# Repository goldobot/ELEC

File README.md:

#ELEC
fichier source des cartes électronique

n'oubliez pas d'ajouter les éléments suivant à la liste gitignore si vous utiliser Altium:
#ignore altium log file
history
*/__Previews
__Previews
Project Logs*

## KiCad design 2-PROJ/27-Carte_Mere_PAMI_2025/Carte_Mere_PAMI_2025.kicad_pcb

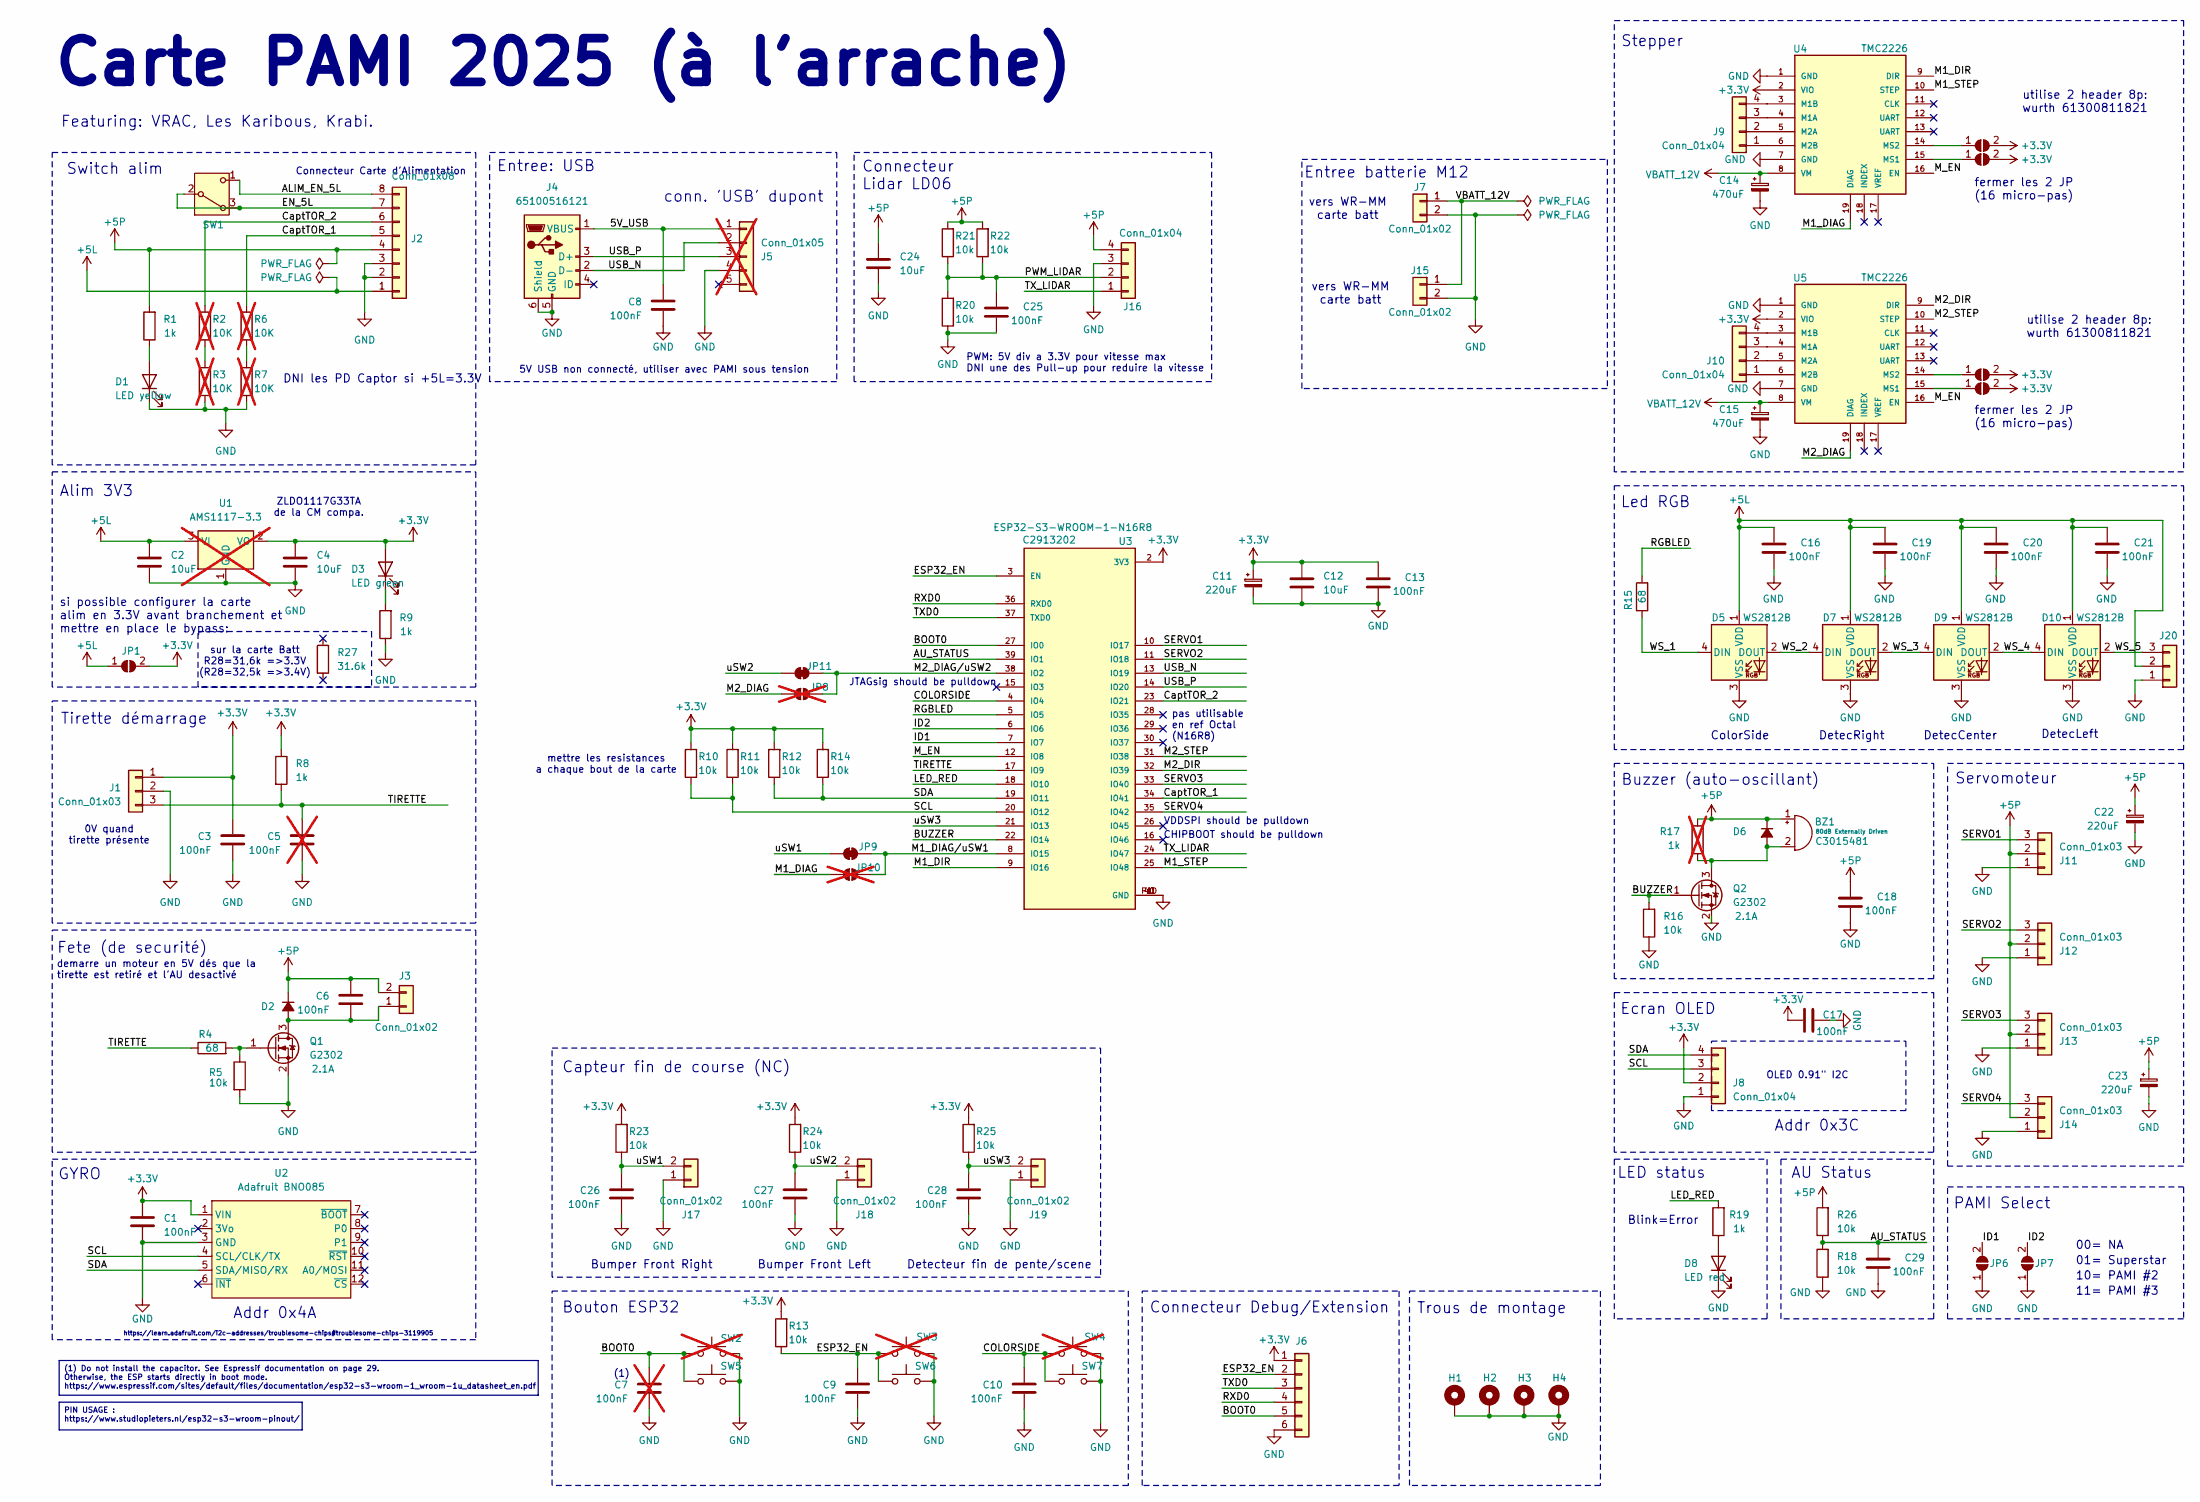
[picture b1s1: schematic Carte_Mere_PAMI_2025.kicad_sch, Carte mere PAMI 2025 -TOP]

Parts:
BZ1: Buzzer; Buzzer_TDK_PS1240P02BT_D12.2mm_H6.5mm; LCSC C3015481
C1, C3, C6, C8, C9, C10, C13, C16, C17, C18, C19, C20, C21, C25, C26, C27, C28, C29: 100nF; C_0603_1608Metric_Pad1.08x0.95mm_HandSolder; LCSC C14663
C2, C4, C12, C24: 10uF; C_0805_2012Metric; LCSC C440198
C5, C7: 100nF; C_0603_1608Metric_Pad1.08x0.95mm_HandSolder; LCSC C14663; not fitted
C11, C22, C23: 220uF; C_Radial_D6.3mm_H11.0mm_P2.50mm
C14, C15: 470uF; C_Radial_D8.0mm_H11.5mm_P3.50mm
D1: LED yellow; LED_0603_1608Metric; LCSC C2290
D2, D6: 1N4148W; D_SOD-123F; LCSC C81598
D3: LED green; LED_0603_1608Metric; LCSC C2290
D5, D7, D9, D10: WS2812B; LED_WS2812B_PLCC4_5.0x5.0mm_P3.2mm
D8: LED red; LED_0603_1608Metric; LCSC C2286
H1, H2, H3, H4: MountingHole_Pad; MountingHole_3.2mm_M3_Pad
J1, J11, J12, J13, J14, J20: Conn_01x03; PinHeader_1x03_P2.54mm_Vertical
J2: Conn_01x08; PinHeader_1x08_P2.54mm_Horizontal
J3, J17, J18, J19: Conn_01x02; PinHeader_1x02_P2.54mm_Vertical
J4: 65100516121; USB_Mini-B_Wuerth_65100516121_Horizontal; LCSC C720611
J5: Conn_01x05; PinHeader_1x05_P2.54mm_Vertical; not fitted
J6: Conn_01x06; PinHeader_1x06_P2.54mm_Vertical
J7, J15: Conn_01x02; SolderWire-0.75sqmm_1x02_P4.8mm_D1.25mm_OD2.3mm
J8: Conn_01x04; Ecran_OLED0.9_Waveshare
J9, J10: Conn_01x04; PinHeader_1x04_P2.54mm_Horizontal
J16: Conn_01x04; PinHeader_1x04_P2.54mm_Vertical
JP1, JP6: ID1; SolderJumper-2_P1.3mm_Open_RoundedPad1.0x1.5mm
JP2, JP4: MS2; SolderJumper-2_P1.3mm_Open_RoundedPad1.0x1.5mm
JP3, JP5: MS1; SolderJumper-2_P1.3mm_Open_RoundedPad1.0x1.5mm
JP7: ID2; SolderJumper-2_P1.3mm_Open_RoundedPad1.0x1.5mm
JP8, JP10: SolderJumper_2_Bridged; R_0402_1005Metric; not fitted
JP9, JP11: SolderJumper_2_Bridged; R_0402_1005Metric_jumperClosed
Q1, Q2: G2302; SOT-23; LCSC C20917
R1, R9, R19: 1k; R_0603_1608Metric_Pad0.98x0.95mm_HandSolder
R2, R3, R6, R7: 10K; R_0603_1608Metric_Pad0.98x0.95mm_HandSolder; LCSC C25804; not fitted
R4, R15: 68; R_0603_1608Metric_Pad0.98x0.95mm_HandSolder; LCSC C23182
R5, R10, R11, R12, R13, R14, R16, R18, R20, R21, R22, R23, R24, R25, R26: 10k; R_0603_1608Metric_Pad0.98x0.95mm_HandSolder; LCSC C25804
R8: 1k; R_0603_1608Metric_Pad0.98x0.95mm_HandSolder; LCSC C21190
R17: 1k; R_0603_1608Metric_Pad0.98x0.95mm_HandSolder; not fitted
R27: 31.6k; R_0603_1608Metric_Pad0.98x0.95mm_HandSolder; Mouser 603-AC0603FR-0731K6L
SW1: SW_DPST_x2; SW_Slide_SPDT_Straight_CK_OS102011MS2Q
SW2, SW3, SW4: SW_Push; SW_Push_1P1T_XKB_TS-1187A; LCSC C318884; not fitted
SW5, SW6, SW7: SW_Push; SW_Push_1TS009xxxx-xxxx-xxxx_6x6x5mm; Mouser 710-430133050816
U1: AMS1117-3.3; SOT-223-3_TabPin2; LCSC C7376; not fitted
U2: Adafruit BNO085
U3: ESP32-S3-WROOM-1-N16R8; PARTREV v1.0; LCSC C2913202
U4, U5: TMC2226; TMC2226_SHIELD

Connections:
+3.3V: C1.1, C3.1, C4.1, C11.1, C12.1, C13.1, C17.1, D3.2 (A), J1.1, J6.1, J8.2, JP1.2 (B), JP2.2 (B), JP3.2 (B), JP4.2 (B), JP5.2 (B), R8.1, R10.2, R11.2, R12.2, R13.2, R14.2, R23.2, R24.2, R25.2, U1.2 (VO), U2.1 (VIN), U3.2 (3V3), U4.2 (VIO), U5.2 (VIO)
+5L: C2.1, C16.1, C19.1, C20.1, C21.1, D5.1 (VDD), D7.1 (VDD), D9.1 (VDD), D10.1 (VDD), J2.1, J20.2, JP1.1 (A), U1.3 (VI)
+5P: BZ1.1 (+), C6.1, C18.1, C22.1, C23.1, C24.1, D2.1 (K), D6.1 (K), J2.4, J3.2, J11.2, J12.2, J13.2, J14.2, J16.4, R1.2, R17.2, R21.2, R22.2, R26.2
/5V_USB: C8.1, J4.1 (VBUS), J5.1
/ALIM_EN_5L: J2.8, SW1.1 (C)
/AU_STATUS: C29.1, R18.2, R26.1, U3.39 (IO1)
/BOOT0: C7.1, J6.5, SW2.1, SW5.1, U3.27 (IO0)
/BUZZER: Q2.1 (G), R16.2, U3.22 (IO14)
/COLORSIDE: C10.1, SW4.1, SW7.1, U3.4 (IO4)
/CaptTOR_1: J2.5, R6.2, U3.34 (IO41)
/CaptTOR_2: J2.6, R2.2, U3.23 (IO21)
/EN_5L: J2.7, SW1.2 (B), SW1.3 (A)
/ESP32_EN: C9.1, J6.2, R13.1, SW3.1, SW6.1, U3.3 (EN)
/ID1: JP6.2 (B), U3.7 (IO7)
/ID2: JP7.2 (B), U3.6 (IO6)
/LED_RED: R19.2, U3.18 (IO10)
/M1_DIAG: JP10.1 (A), U4.19 (DIAG)
/M1_DIAG/uSW1: JP9.2 (B), JP10.2 (B), U3.8 (IO15)
/M1_DIR: U3.9 (IO16), U4.9 (DIR)
/M1_STEP: U3.25 (IO48), U4.10 (STEP)
/M2_DIAG: JP8.1 (A), U5.19 (DIAG)
/M2_DIAG/uSW2: JP8.2 (B), JP11.2 (B), U3.38 (IO2)
/M2_DIR: U3.32 (IO39), U5.9 (DIR)
/M2_STEP: U3.31 (IO38), U5.10 (STEP)
/M_EN: U3.12 (IO8), U4.16 (EN), U5.16 (EN)
/PWM_LIDAR: C25.1, J16.2, R20.2, R21.1, R22.1
/RGBLED: R15.2, U3.5 (IO5)
/RXD0: J6.4, U3.36 (RXD0)
/SCL: J8.3, R10.1, R11.1, U2.4 (SCL/CLK/TX), U3.20 (IO12)
/SDA: J8.4, R12.1, R14.1, U2.5 (SDA/MISO/RX), U3.19 (IO11)
/SERVO1: J11.3, U3.10 (IO17)
/SERVO2: J12.3, U3.11 (IO18)
/SERVO3: J13.3, U3.33 (IO40)
/SERVO4: J14.3, U3.35 (IO42)
/TIRETTE: C5.1, J1.3, R4.1, R8.2, U3.17 (IO9)
/TXD0: J6.3, U3.37 (TXD0)
/TX_LIDAR: J16.1, U3.24 (IO47)
/USB_N: J4.2 (D-), J5.2, U3.13 (IO19)
/USB_P: J4.3 (D+), J5.3, U3.14 (IO20)
/WS_1: D5.4 (DIN), R15.1
/WS_2: D5.2 (DOUT), D7.4 (DIN)
/WS_3: D7.2 (DOUT), D9.4 (DIN)
/WS_4: D9.2 (DOUT), D10.4 (DIN)
/WS_5: D10.2 (DOUT), J20.3
/uSW1: C26.1, J17.2, JP9.1 (A), R23.1
/uSW2: C27.1, J18.2, JP11.1 (A), R24.1
/uSW3: C28.1, J19.2, R25.1, U3.21 (IO13)
GND: C1.2, C2.2, C3.2, C4.2, C5.2, C7.2, C8.2, C9.2, C10.2, C11.2, C12.2, C13.2, C14.2, C15.2, C16.2, C17.2, C18.2, C19.2, C20.2, C21.2, C22.2, C23.2, C24.2, C25.2, C26.2, C27.2, C28.2, C29.2, D1.1 (K), D5.3 (VSS), D7.3 (VSS), D8.1 (K), D9.3 (VSS), D10.3 (VSS), H1.1, H2.1, H3.1, H4.1, J1.2, J2.2, J2.3, J4.5 (GND), J4.6 (Shield), J5.4, J6.6, J7.2, J8.1, J11.1, J12.1, J13.1, J14.1, J15.2, J16.3, J17.1, J18.1, J19.1, J20.1, JP6.1 (A), JP7.1 (A), Q1.2 (S), Q2.2 (S), R3.1, R5.2, R7.1, R9.1, R16.1, R18.1, R20.1, SW2.2, SW3.2, SW4.2, SW5.2, SW6.2, SW7.2, U1.1 (GND), U2.3 (GND), U3.1 (GND), U3.40 (GND), U3.PAD (GND), U4.1 (GND), U4.7 (GND), U5.1 (GND), U5.7 (GND)
unnamed: BZ1.2 (-), D6.2 (A), Q2.3 (D), R17.1
unnamed: D1.2 (A), R1.1
unnamed: C6.2, D2.2 (A), J3.1, Q1.3 (D)
unnamed: D3.1 (K), R9.2
unnamed: D8.2 (A), R19.1
unnamed: J9.1, U4.6 (M2B)
unnamed: J9.2, U4.5 (M2A)
unnamed: J9.3, U4.4 (M1A)
unnamed: J9.4, U4.3 (M1B)
unnamed: J10.1, U5.6 (M2B)
unnamed: J10.2, U5.5 (M2A)
unnamed: J10.3, U5.4 (M1A)
unnamed: J10.4, U5.3 (M1B)
unnamed: JP2.1 (A), U4.14 (MS2)
unnamed: JP3.1 (A), U4.15 (MS1)
unnamed: JP4.1 (A), U5.14 (MS2)
unnamed: JP5.1 (A), U5.15 (MS1)
unnamed: Q1.1 (G), R4.2, R5.1
unnamed: R2.1, R3.2
unnamed: R6.1, R7.2
VBATT_12V: C14.1, C15.1, J7.1, J15.1, U4.8 (VM), U5.8 (VM)

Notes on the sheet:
(1) Do not install the capacitor. See Espressif documentation on page 29. Otherwise, the ESP starts directly in boot mode. https://www.espressif.com/sites/default/files/documentation/esp32-s3-wroom-1_wroom-1u_datasheet_en.pdf
PIN USAGE : https://www.studiopieters.nl/esp32-s3-wroom-pinout/
Stepper
Connecteur Carte d'Alimentation
Tirette démarrage
DetecLeft
Servomoteur
GYRO
fermer les 2 JP (16 micro-pas)
vers WR-MM carte batt
CHIPBOOT should be pulldown
Trous de montage
LED status
ZLDO1117G33TA de la CM compa.
demarre un moteur en 5V dés que la tirette est retiré et l'AU desactivé
Featuring: VRAC, Les Karibous, Krabi.
Blink=Error
Addr 0x4A
Carte PAMI 2025 (à l'arrache)
OLED 0.91" I2C
Ecran OLED
00= NA
0V quand tirette présente
Alim 3V3
AU Status
utilise 2 header 8p: wurth 61300811821
Fete (de securité)
Led RGB
pas utilisable en ref Octal (N16R8)
Capteur fin de course (NC)
Bumper Front Right
DetecCenter
ColorSide
Connecteur Debug/Extension
Addr 0x3C
conn. 'USB' dupont
mettre les resistances a chaque bout de la carte
11= PAMI #3
Connecteur Lidar LD06
Entree batterie M12

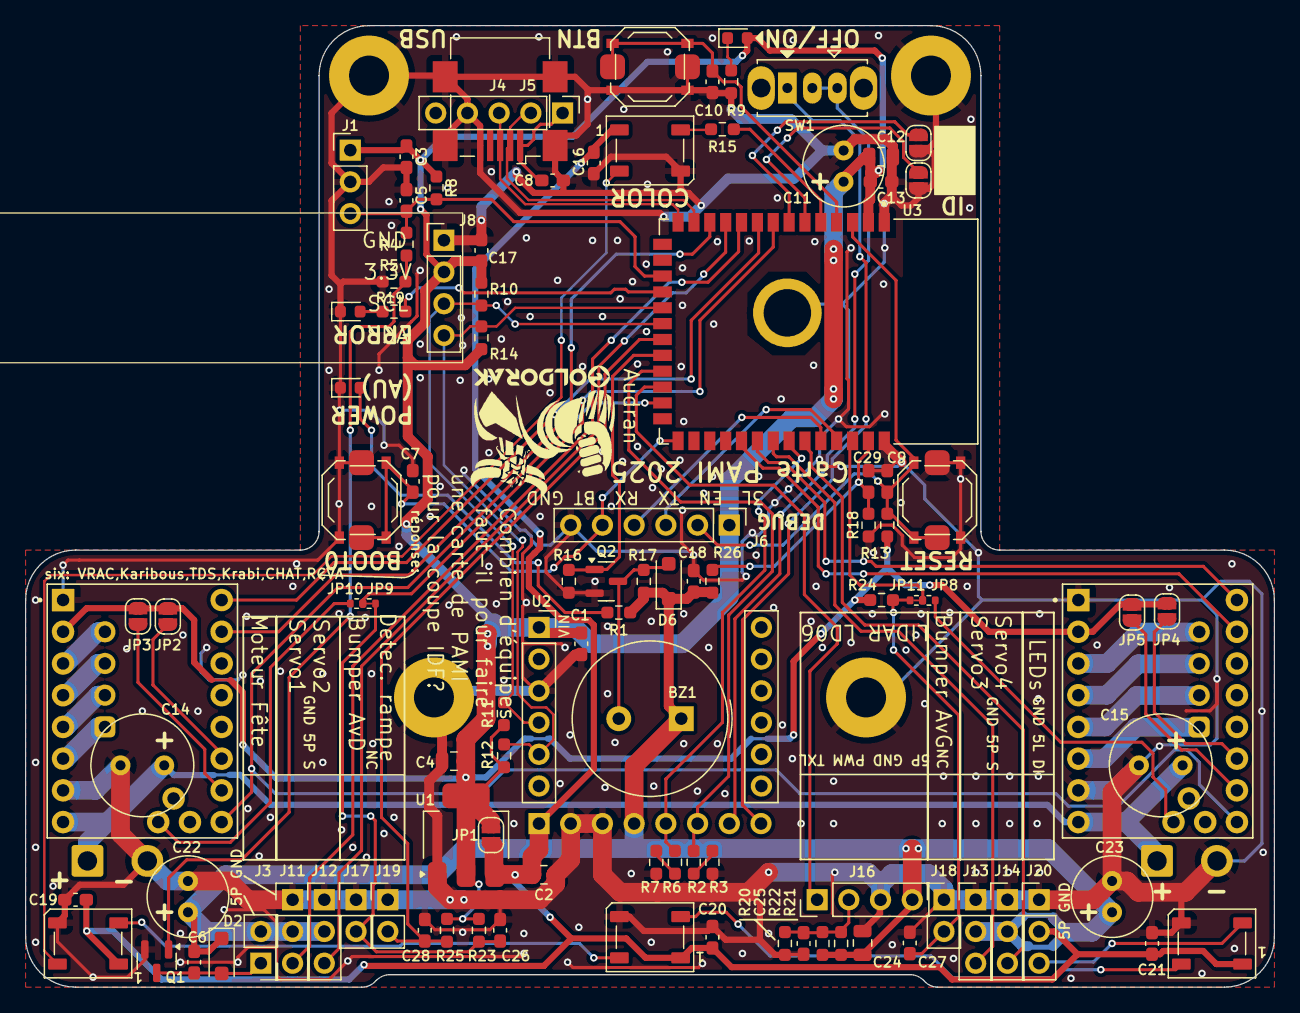
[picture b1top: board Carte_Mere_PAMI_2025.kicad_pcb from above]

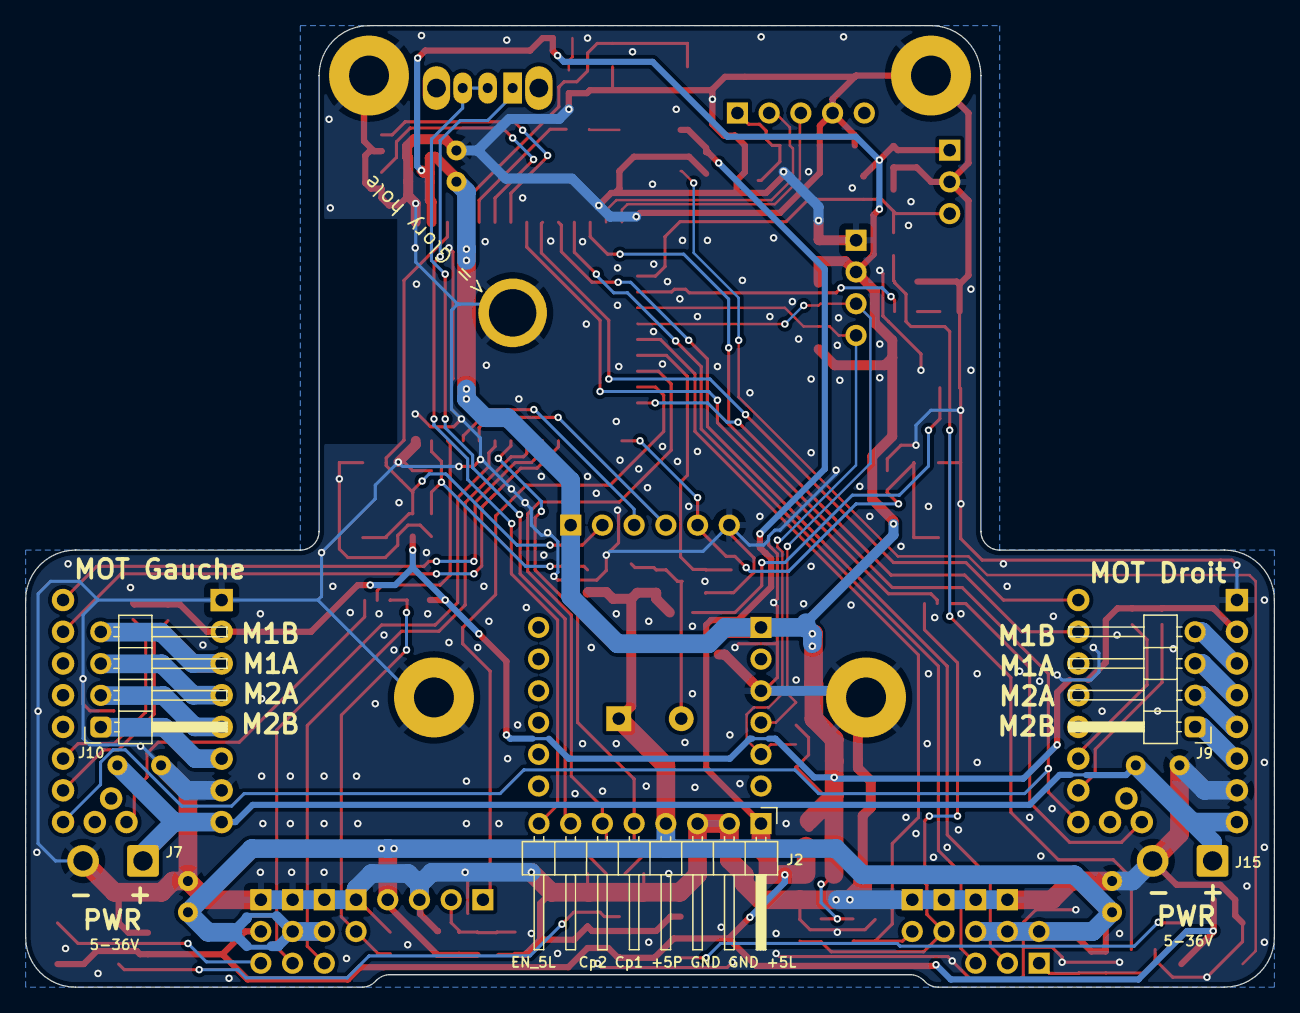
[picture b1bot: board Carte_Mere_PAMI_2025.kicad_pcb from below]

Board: 2 copper layers, 100.0 x 77.0 mm, 114 parts (5 on the bottom side), 69 nets.

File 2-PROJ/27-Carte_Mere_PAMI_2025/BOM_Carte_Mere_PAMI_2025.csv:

"Reference";"Value";"Qty";"DNP";"Mouser"
"BZ1";"Buzzer";"1";"";""
"C1,C3,C6,C8,C9,C10,C13,C16,C17,C18,C19,C20,C21,C25,C26,C27,C28,C29";"100nF";"18";"";""
"C2,C4,C12,C24";"10uF";"4";"";"81-GRM21BR61H106KE3L"
"C11,C22,C23";"220uF";"3";"";""
"C14,C15";"470uF";"2";"";""
"D1";"LED yellow";"1";"";"710-150060YS75000"
"D2,D6";"1N4148W";"2";"";"621-1N4148W-F"
"D3";"LED green";"1";"";"710-150060VS75000"
"D5,D7,D9,D10";"WS2812B";"4";"";""
"D8";"LED red";"1";"";""
"J1,J11,J12,J13,J14,J20";"Conn_01x03";"6";"";""
"J2";"Conn_01x08";"1";"";""
"J3,J17,J18,J19";"Conn_01x02";"4";"";""
"J4";"65100516121";"1";"";"710-65100516121"
"J6";"Conn_01x06";"1";"";""
"J8,J9,J10,J16";"Conn_01x04";"4";"";""
"JP1,JP6";"ID1";"2";"";""
"JP2,JP4";"MS2";"2";"";""
"JP3,JP5";"MS1";"2";"";""
"JP7";"ID2";"1";"";""
"Q1,Q2";"G2302";"2";"";"621-DMG2302UK-7"
"R1,R8,R9,R19";"1k";"4";"";""
"R4,R15";"68";"2";"";"603-RC0603FR-1068RL"
"R5,R10,R11,R12,R13,R14,R16,R18,R20,R21,R22,R23,R24,R25,R26";"10k";"15";"";""
"R27";"31.6k";"1";"";"603-AC0603FR-0731K6L"
"SW1";"SW_DPST_x2";"1";"";""
"SW5,SW6,SW7";"SW_Push";"3";"";"710-430133050816"
"U2";"Adafruit BNO085";"1";"";""
"U3";"ESP32-S3-WROOM-1-N16R8";"1";"";""
"U4,U5";"TMC2226";"2";"";""

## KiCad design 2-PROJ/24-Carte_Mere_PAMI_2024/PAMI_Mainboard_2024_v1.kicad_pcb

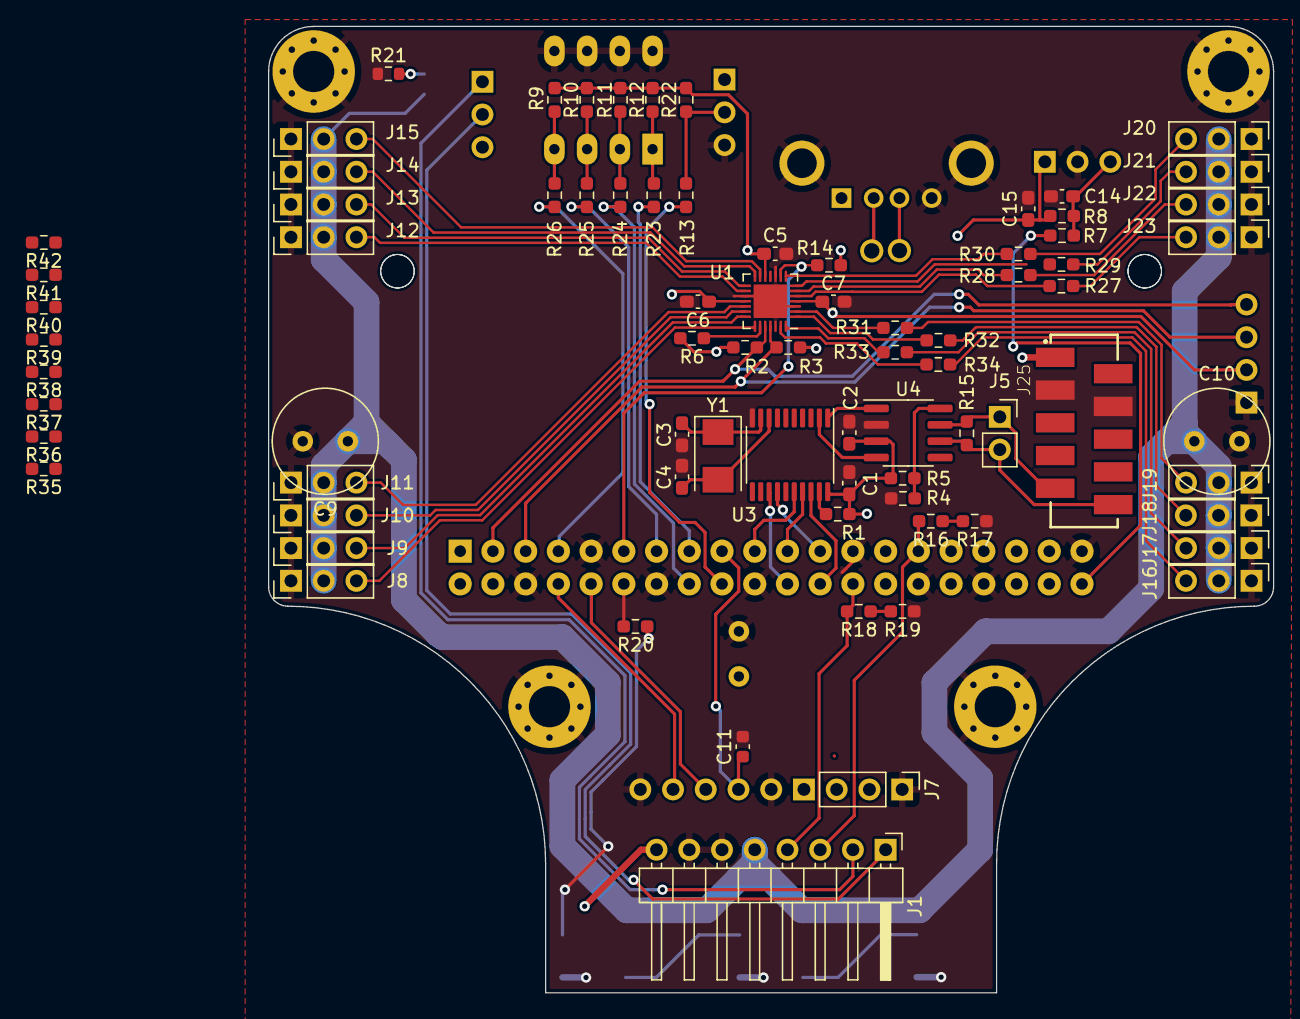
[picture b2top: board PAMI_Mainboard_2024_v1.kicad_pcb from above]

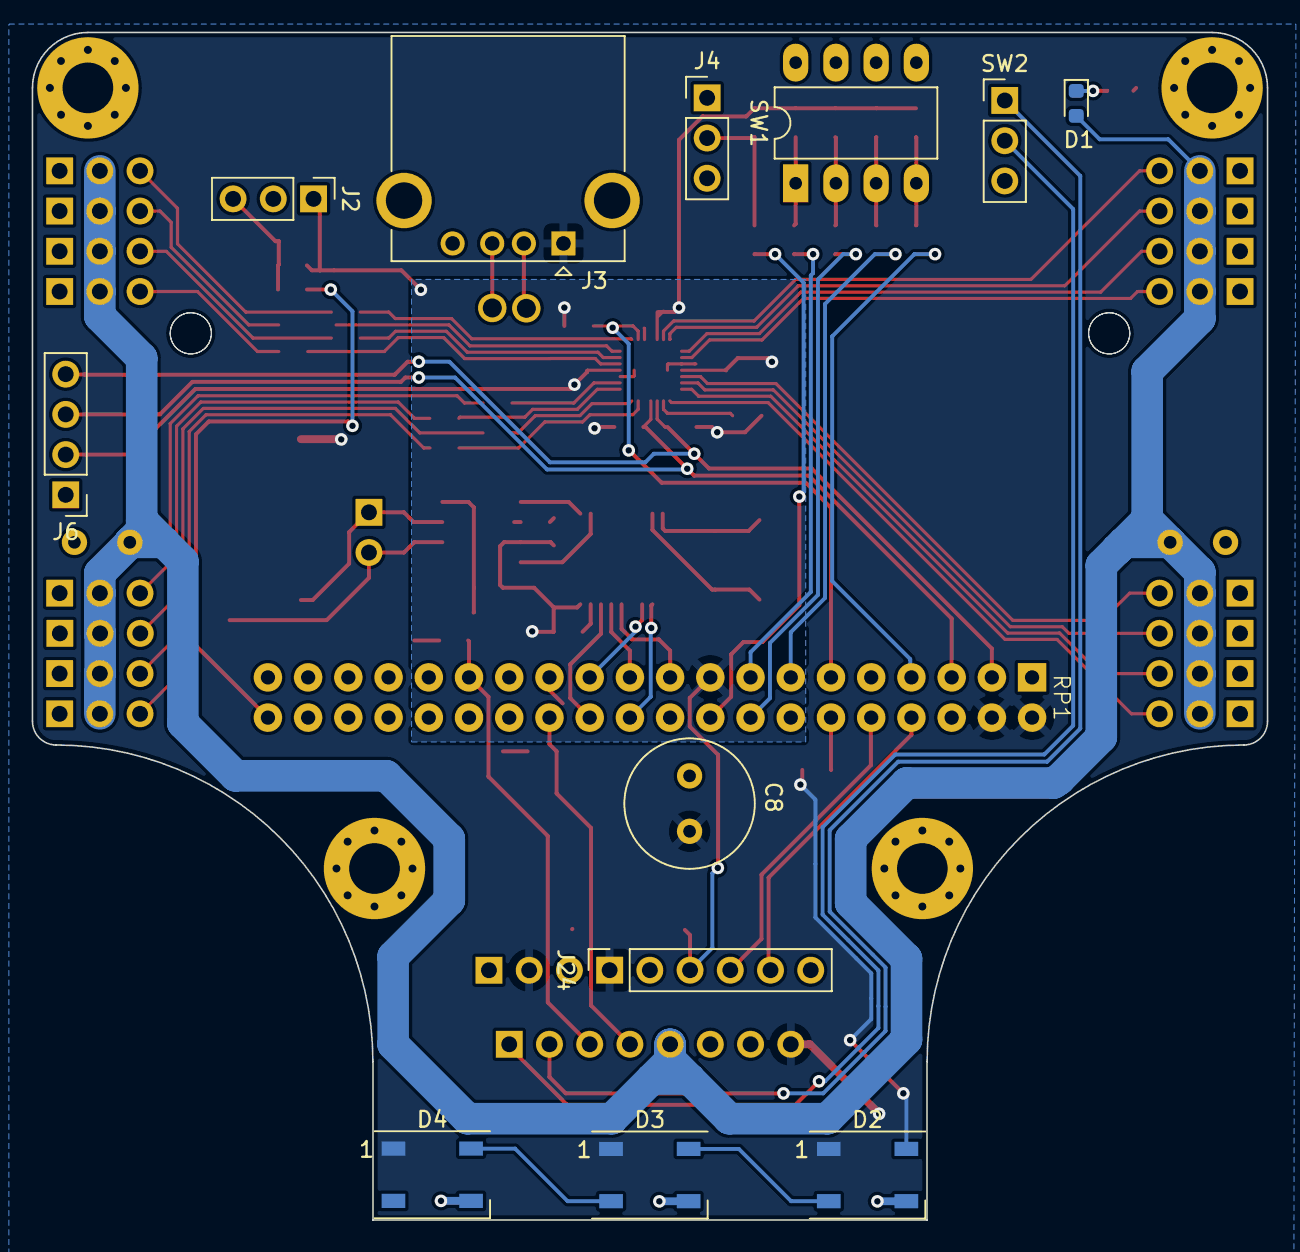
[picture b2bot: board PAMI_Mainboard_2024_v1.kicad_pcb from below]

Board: 2 copper layers, 78.0 x 75.0 mm, 96 parts (14 on the bottom side), 81 nets.

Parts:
C1, C2, C5, C6, C7, C14, C15: 100nF; C_0603_1608Metric_Pad1.08x0.95mm_HandSolder
C3, C4: 22pF; C_0603_1608Metric_Pad1.08x0.95mm_HandSolder
C8, C9, C10: 470uF; C_Radial_D8.0mm_H11.5mm_P3.50mm
C11: 100nF; C_0603_1608Metric
D1: LED; LED_0603_1608Metric
D2, D3, D4: WS2812B; LED_WS2812B_PLCC4_5.0x5.0mm_P3.2mm
H1, H2, H3, H4: MountingHole_Pad; MountingHole_3.2mm_M3_Pad_Via
J1: Conn_01x08; PinHeader_1x08_P2.54mm_Horizontal
J2, J4, J7, J8, J9, J10, J11, J12, J13, J14, J15, J16, J17, J18, J19, J20, J21, J22, J23: Conn_01x03; PinHeader_1x03_P2.54mm_Vertical
J3: USB_A; USB_A_CONNFLY_DS1095-WNR0
J5: Conn_01x02; PinSocket_1x02_P2.54mm_Vertical
J6: Conn_01x04; PinHeader_1x04_P2.54mm_Vertical
J24: Conn_01x06; PinSocket_1x06_P2.54mm_Vertical
J25: Conn_02x05_Odd_Even; 690357281076
R1, R2, R3, R4, R5, R6, R8, R9, R10, R11, R12, R14, R16, R17, R18, R19, R22: 10K; R_0603_1608Metric_Pad0.98x0.95mm_HandSolder
R7, R20: 68; R_0603_1608Metric_Pad0.98x0.95mm_HandSolder
R13, R23, R24, R25, R26, R27, R28, R29, R30, R31, R32, R33, R34, R35, R36, R37, R38, R39, R40, R41, R42: 1K; R_0603_1608Metric_Pad0.98x0.95mm_HandSolder
R15: 120; R_0603_1608Metric_Pad0.98x0.95mm_HandSolder
R21: 1K; R_0603_1608Metric
RP1: Raspberry_Pi_Zero
RP_USB1: Raspberry_Pi_Zero_USB_Pads
SW1: SW_DIP_x04; DIP-8_W7.62mm_LongPads
SW2: SW_DPST_x2; PinHeader_1x03_P2.54mm_Vertical
U1: QFN-28-1EP_4x4mm_P0.4mm_EP2.6x2.6mm_ThermalVias
U3: MCP2515-xST; TSSOP-20_4.4x6.5mm_P0.65mm
U4: MCP2551-I-SN; SOIC-8_3.9x4.9mm_P1.27mm
Y1: 16 MHz; Crystal_SMD_5032-2Pin_5.0x3.2mm

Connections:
+3.3VP: C1.1, C2.1, C5.1, C6.1, C7.1, C11.1, C15.1, J2.1, J6.2, J24.3, R1.2, R2.2, R3.2, R4.2, R6.2, R8.2, R9.2, R10.2, R11.2, R12.2, R14.2, R22.2, RP1.17 (3V3), U1.4 (VCC1), U1.12 (VDDM), U1.18 (VCC2), U3.20 (VDD), U4.3 (VDD)
+5P: C9.1, C10.1, D1.2 (A), J1.5, J8.2, J9.2, J10.2, J11.2, J12.2, J13.2, J14.2, J15.2, J16.2, J17.2, J18.2, J19.2, J20.2, J21.2, J22.2, J23.2
+5V: C8.1, D2.1 (VDD), D3.1 (VDD), D4.1 (VDD), J1.8, J3.1 (VBUS), J7.2, J24.1, J25.1, RP1.2 (5V), RP1.4 (5V)
/ALIM_EN_5L: J1.1, SW2.2 (B)
/CAN/CANH: J5.1, J25.9, R15.2, U4.7 (CANH)
/CAN/CANL: J5.2, J25.10, R15.1, U4.6 (CANL)
/CAN/CE: RP1.24 (GPIO8/SPI0_CE0), U3.18 (~CS)
/CAN/MISO: RP1.21 (GPIO9/SPI0_MISO), U3.17 (SO)
/CAN/MOSI: RP1.19 (GPIO10/SPI0_MOSI), U3.16 (SI)
/CAN/SCK: RP1.23 (GPIO11/SPI0_SCK), U3.14 (SCK)
/CaptTOR_1: J1.4, R18.2, RP1.26 (GPIO7/SPI0_CE1)
/CaptTOR_2: J1.3, R16.2, RP1.29 (GPIO5/GPCLK1)
/EN_5L: J1.2, SW2.1 (A)
/INT_CAN: RP1.22 (GPIO25), U3.13 (~INT)
/INT_SX: R14.1, RP1.11 (GPIO17/SPI1_CE1), U1.9 (INT)
/SIDE: R13.2, RP1.18 (GPIO24)
/SX1509/SCL: J6.3, R3.1, RP1.5 (GPIO3/I2C1_SCL), U1.25 (SCL)
/SX1509/SDA: J6.4, R2.1, RP1.3 (GPIO2/I2C1_SDA), U1.24 (SDA)
/SX1509/SX_IO_0: R34.1, U1.27 (IO_0)
/SX1509/SX_IO_1: R33.1, U1.28 (IO_1)
/SX1509/SX_IO_2: R32.1, U1.1 (IO_2)
/SX1509/SX_IO_3: R31.1, U1.2 (IO_3)
/SX1509/SX_IO_4: R27.1, U1.5 (IO_4)
/SX1509/SX_IO_5: R28.1, U1.6 (IO_5)
/SX1509/SX_IO_6: R29.1, U1.7 (IO_6)
/SX1509/SX_IO_7: R30.1, U1.8 (IO_7)
/SX1509/SX_IO_8: R42.2, U1.13 (IO_8)
/SX1509/SX_IO_9: R41.2, U1.14 (IO_9)
/SX1509/SX_IO_10: R40.2, U1.15 (IO_10)
/SX1509/SX_IO_11: R39.2, U1.16 (IO_11)
/SX1509/SX_IO_12: R38.2, U1.19 (IO_12)
/SX1509/SX_IO_13: R37.2, U1.20 (IO_13)
/SX1509/SX_IO_14: R36.2, U1.21 (IO_14)
/SX1509/SX_IO_15: R35.2, U1.22 (IO_15)
/TIRETTE: R7.2, RP1.40 (GPIO21/SPI1_SCK)
/WS2812B: R20.2, RP1.12 (GPIO18/SPI1_CE0)
GND: C1.2, C2.2, C3.2, C4.2, C5.2, C6.2, C7.2, C8.2, C9.2, C10.2, C11.2, C14.2, C15.2, D2.3 (VSS), D3.3 (VSS), D4.3 (VSS), H1.1, H2.1, H3.1, H4.1, J1.6, J1.7, J2.2, J3.4 (GND), J3.5 (Shield), J4.3, J6.1, J7.1, J8.1, J9.1, J10.1, J11.1, J12.1, J13.1, J14.1, J15.1, J16.1, J17.1, J18.1, J19.1, J20.1, J21.1, J22.1, J23.1, J24.2, J24.6, J25.3, J25.4, R5.1, R17.1, R19.1, R21.1, RP1.6 (GND), RP1.9 (GND), RP1.14 (GND), RP1.20 (GND), RP1.25 (GND), RP1.30 (GND), RP1.34 (GND), RP1.39 (GND), SW1.5, SW1.6, SW1.7, SW1.8, U1.3 (GND), U1.10 (ADDR1), U1.17 (GND), U1.26 (ADDR0), U1.29 (GND_PAD), U3.10 (VSS), U4.2 (VSS)
unnamed: D1.1 (K), R21.2
unnamed: D2.4 (DIN), R20.1
unnamed: D2.2 (DOUT), D3.4 (DIN)
unnamed: D3.2 (DOUT), D4.4 (DIN)
unnamed: D4.2 (DOUT), J7.3
unnamed: C14.1, J2.3, R7.1, R8.1
unnamed: J3.3 (D+), RP_USB1.1 (USB_DP)
unnamed: J3.2 (D-), RP_USB1.2 (USB_DM)
unnamed: J4.2, R13.1, R22.1
unnamed: J8.3, R35.1
unnamed: J9.3, R36.1
unnamed: J10.3, R37.1
unnamed: J11.3, R38.1
unnamed: J12.3, R39.1
unnamed: J13.3, R40.1
unnamed: J14.3, R41.1
unnamed: J15.3, R42.1
unnamed: J16.3, R34.2
unnamed: J17.3, R33.2
unnamed: J18.3, R32.2
unnamed: J19.3, R31.2
unnamed: J20.3, R27.2
unnamed: J21.3, R28.2
unnamed: J22.3, R29.2
unnamed: J23.3, R30.2
unnamed: J24.4, RP1.10 (GPIO15/UART_RX)
unnamed: J24.5, RP1.8 (GPIO14/UART_TX)
unnamed: R10.1, R25.1, SW1.3
unnamed: R11.1, R24.1, SW1.2
unnamed: R12.1, R23.1, SW1.1
unnamed: R16.1, R17.2
unnamed: R18.1, R19.2
unnamed: R9.1, R26.1, SW1.4
unnamed: R26.2, RP1.7 (GPIO4/GPCLK0)
unnamed: R23.2, RP1.15 (GPIO22)
unnamed: R24.2, RP1.16 (GPIO23)
unnamed: R25.2, RP1.13 (GPIO27)
unnamed: R6.1, U1.23 (RESET)
unnamed: C4.1, U3.9 (OSC1), Y1.1
unnamed: C3.1, U3.8 (OSC2), Y1.2
unnamed: U3.2 (RXCAN), U4.4 (RXD)
unnamed: U3.1 (TXCAN), U4.1 (TXD)
unnamed: R1.1, U3.19 (~RESET)
unnamed: R4.1, R5.2, U4.8 (Rs)

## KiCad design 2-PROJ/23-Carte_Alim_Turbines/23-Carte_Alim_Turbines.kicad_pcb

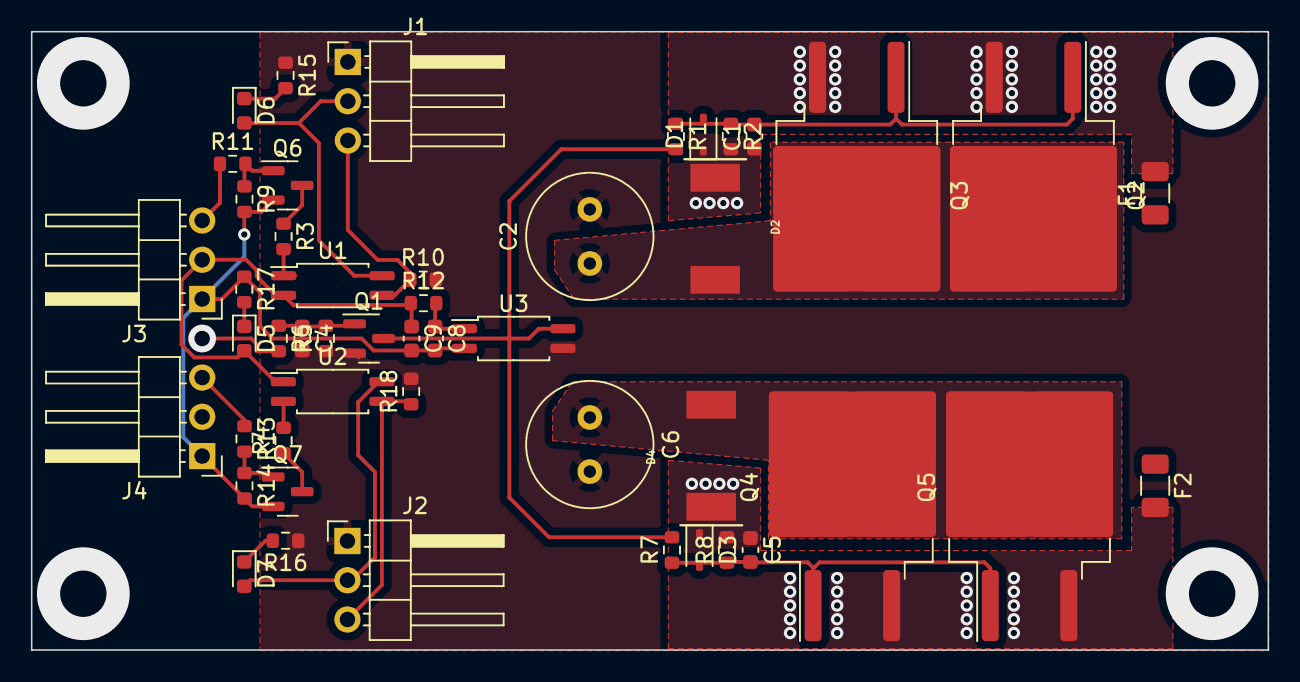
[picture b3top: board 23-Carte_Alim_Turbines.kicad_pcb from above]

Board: 2 copper layers, 80.0 x 40.0 mm, 48 parts (0 on the bottom side), 28 nets.

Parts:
C1, C4, C5, C8: 100nF; C_0603_1608Metric
C2, C6: 470uF; C_Radial_D8.0mm_H11.5mm_P3.50mm
C9: 10µF; C_0603_1608Metric
D1, D3: 14.6V; D_SOD-323
D2, D4: DO-214AB
D5, D6, D7: LED; LED_0603_1608Metric
F1, F2: 40A (SF-1206HV40M-2); Fuse_1206_3216Metric
J1, J2, J3, J4: Conn_01x03; PinHeader_1x03_P2.54mm_Horizontal
Q1, Q6, Q7: 2N7002; SOT-23
Q2, Q3, Q4, Q5: SUM110P06-08L; TO-263-2
R1, R2, R7, R8: 10k; R_0603_1608Metric
R3, R4, R10, R11, R12, R13, R15, R16, R17, R18: R; R_0603_1608Metric
R5, R9, R14: 100k; R_0603_1608Metric
R6: 47k; R_0603_1608Metric
U1, U2, U3: ACPL-214-500E; SOP-4_4.4x2.6mm_P1.27mm

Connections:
/5P: C9.1, D5.2 (A), J3.2, R12.1, U1.2, U2.1
/5V_ESC_T1: D6.2 (A), J1.2, U1.4
/5V_ESC_T2: D7.2 (A), J2.2, U2.4
/PWR_T1: C2.1, D2.2 (A), Q2.2 (D), Q3.2 (D)
/PWR_T2: C6.1, D4.2 (A), Q4.2 (D), Q5.2 (D)
/VBATT_24V: F1.1, F2.1
/VBATT_24V_T1: C1.1, D1.1 (K), D2.1 (K), F1.2, Q2.3 (S), Q3.3 (S), R2.2
/VBATT_24V_T2: C5.1, D3.1 (K), D4.1 (K), F2.2, Q4.3 (S), Q5.3 (S), R8.2
GND: C8.2, C9.2, J3.1, J4.1, Q6.2 (S), Q7.2 (S), R9.2, R14.2, R17.1, U3.2
GNDPWR: C2.2, C4.2, C6.2, J1.1, J2.1, Q1.2 (S), R5.1, R10.2, R15.1, R16.1, R18.2, U3.3
unnamed: C8.1, R12.2, U3.1
unnamed: C1.2, D1.2 (A), Q2.1 (G), Q3.1 (G), R1.1, R2.1
unnamed: C5.2, D3.2 (A), Q4.1 (G), Q5.1 (G), R7.1, R8.1
unnamed: D5.1 (K), R17.2
unnamed: D6.1 (K), R15.2
unnamed: D7.1 (K), R16.2
unnamed: J1.3, R10.1, U1.3
unnamed: J2.3, R18.1, U2.3
unnamed: J3.3, R11.1
unnamed: J4.3, R13.1
unnamed: Q1.3 (D), R1.2, R7.2, U3.4
unnamed: C4.1, Q1.1 (G), R5.2, R6.1
unnamed: Q6.3 (D), R3.1
unnamed: Q6.1 (G), R9.1, R11.2
unnamed: Q7.3 (D), R4.1
unnamed: Q7.1 (G), R13.2, R14.1
unnamed: R3.2, U1.1
unnamed: R4.2, U2.2

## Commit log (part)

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2017-11-23 ajout initial des librairie et projet 2017 (partiel)
2017-11-23 correction
2017-11-25 ajout des autres projet de 2017, ajout du workspace et des autres paramètres et modèle
2017-11-25 mise à jour du workspace, de chemin de fichier ajout de la liste des composants_a_creer de 2017
2017-11-25 suppression des desktop.ini
2017-12-05 ajout d'élément pour la mesure de courant
2017-12-05 organisation des lignes de Current Sense
2017-12-05 répartition des feuilles entre CartApuce etCartOgraphie
2017-12-12 Ajout de la majorité des signaux sur les feuilles CoG,CaP Petite correction (CC, BreakOut2017)... Ajout d'empreinte aux lib Ajout d'un pinout du STM32F767 du BreakOut2017
2017-12-13 ajout des cartes 2017 v2 faites par Goldo
2017-12-15 Ajout de la liste des choses à faire.
2017-12-15 Ajout des composants requis pour la carte de barriere
2017-12-15 Correction du symbole du transistor.
2017-12-15 Ajout du circuit électronique pour la barrière.
2017-12-17 ajout de l'empreinte mise à jour du DE0 nano.
2017-12-17 ajout du projet carte barriere au workspace
2017-12-18 ajout DE0
2018-01-07 Ajout de connecteur au lib Modification connecteur carte capteur (+PDF)
2018-01-08 ajout de ref à créer
2018-01-12 Ajout capteurs BPW34
2018-01-12 Correction du schéma du BPW34.
2018-01-12 Création de la schématique et du circuit imprimé carte barrière optique.
2018-01-12 Création de la carte d'interface.
2018-01-14 Création de la schématique de la carte et initialisation du PCB.
2018-01-14 Réannotation de la schématique.
2018-01-14 Suppression du fichier de routage.
2018-01-14 Revert "Suppression du fichier de routage."
    This reverts commit b4e968843c6100b1bcbdef7a1b5f4c1b083207a0.
2018-01-14 Recréation du fichier PcbDoc
2018-01-16 Conception v1 de la carte.
2018-01-21 Relecture Audran
2018-01-21 Ajout des modifs demandées par Audran.
2018-01-21 Corrections demandées par Audran.
2018-01-22 Sauvegarde du fichier.
2018-01-23 Fin du retravail de la carte barrière optique.
2018-01-23 Revert "Fin du retravail de la carte barrière optique."
    This reverts commit 0435c9675cfd4a5042f8762fc307af3d349afec9.
2018-01-23 Fin du retravail de la carte barriere optique.
2018-01-26 Finalisation de la carte d'Audran.
2018-02-04 retravail du routage de gregoire. (et swap des signaux)
2018-02-17 Ajout de SI3410DV
2018-02-18 Travail en cours sur la carte a puce
2018-02-18 Progression dans la conception de la carte a puce
2018-02-20 relecture CDC et PWR sur CaP (nb: la case n'est pas pris en compte dans les noms pour GIT: CaP=CAp, donc pas d'update si ce changement est fait)
2018-02-20 Correction du symbole d'un MOSFET.
2018-02-20 Correction du symbole d'un pont en h
2018-03-01 Ajout de la résistance de shunt de 0.030 en 1206.
2018-03-01 Ajout de 620ohm en 0402
2018-03-01 Ajout des circuits de mesure de courant des ponts en H.
2018-03-01 Modification de la résistance de mesure de courant.
2018-03-01 Correction des erreurs relevées par Audran
2018-03-01 Travail sur INA et INB et mesure de courant. Correction du schéma pour correspondre à la référence de ST. Correction des INA et INB. Reglage de la resistance pour la mesure du courant, et ajout d'une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
2018-03-01 Cablage des servos.
2018-03-06 Ajout de la diode schottky à la bibliothèque.
2018-03-09 Correction de la tension pour EN/Diag-X.
2018-03-09 Signaux moteurs liés dans pont en H.
2018-03-09 Correction des noms des mesures du courant.
2018-03-09 Ajout d'un message d'avertissement pour le filtre de l'alimentation.
2018-03-11 Correction de lien au lib (avant update). correction fichier projet (lib manquante)
2018-03-11 correction de l'empreinte pont en H, update composant et correction bug bouchon CAN sur CoG_STM
2018-03-11 modification du PCB capteur couleur (maj FP DRV8838)
2018-03-11 Modification des diodes de la bibliothèque pour une fusion.
2018-03-11 Ajout de la diode schottky BAT54S-7-F.
2018-04-24 fin sch, debut pcb de la carte EV
2018-04-24 fin v1 routage carte EV
2018-04-24 creation d'un template de BOM, generation d'une BOM et retouche Mineure du PCB Carte EV et Diode.IntLib
2018-08-18 ajout de la librairie de Relais
2018-08-28 correction sur la lib connecteur et diode. ajout d'un connecteur DB9
2018-09-01 correction couche 13 sur 1
2019-03-03 mise à jour des pcb (version fabriqué pour 2019)
2019-03-17 ajout v1 carte alim 2019
2019-03-18 carte alim 2019: ajout de ref de composant
2019-03-21 ajout de 4 ferrite, debut du placement, DNI, gen BOM et pdf
2019-03-21 placement #1 de la carte alim 2019
2019-03-21 suite placement clavier
2019-03-22 routage carte alim #1
2019-03-23 routage carte alim #2
2019-03-24 routage carte alim #4 (ajout via et finition polygon. debut serigraphie)
2019-03-24 ajout d'une note sur les futures commandes de composant
2019-03-25 routage carte alim #5
2019-03-26 routage carte alim #6 et fichier de prod
2019-03-28 Maj BOM
2019-03-31 Maj BOM en prevision de la commande
2019-04-01 Maj BOM et Workspace
2019-04-06 Maj BOM et projet avec variante de fabrication
2020-01-25 ajout de note sur les correction de la carte alim 2019 + initiation de la CM2020
2020-03-17 Update supplier
2020-03-21 JLCPCB references
2020-03-21 JLCPCB ref
2020-03-21 JLCPCB refs
2020-03-21 ajout de composant à creer
2020-03-22 JLCPCB refs mises
2020-03-22 Updating and creating components
2020-04-24 Maj HSI + Nouvelle modif CA_2020
2020-05-03 Ajout du TVS 82400274 (a valider)
2020-05-03 Mise à jour de la carte alimentation: - correction des capa sur les signaux (partie capteur) - remplacement des ferrite 0603 par 0805 (partie alim-capteur) - mise à jour du montage Mosfet P de puissa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
2020-05-03 mise en conformité de la lib diode
2020-05-09 Part 2 de la maj de la carte alimentation
2020-05-10 suppression de fichier temporaire indument commité
2020-05-10 completion de lib avec les LDO
2020-05-13 Mise à jour routage partie clavier (TODO: serigraphie + verif collision et finale)
2020-05-17 Ajout carte herse v1
2020-05-21 ajout de l'architecture electronique du robot 2020 (Diagrams.net)
2020-05-22 updated architecture (cleaned, net name corrected)
2020-05-23 Maj Carte Herse
2020-05-24 renommage carte Alim
2020-05-24 Maj lib condensateur (ménage, footprint, JLCPCB parts)
2020-05-24 MaJ lib Resistance, Condensateu, Diode, Opto, Alim
2020-05-27 Creation de la lib archive (trop de composant obsolete dans les lib, un peu de ménage)
2020-05-30 Suite de la mise en archive et mise à jour des libs
2020-05-31 Fin de la mise à jour des bibliothèque de composant (sauf coquille).
2020-06-01 Changement couleur des leds (et resistance), remplacement ref Mosfet N, ajustement des DNI.
2020-06-01 Correction des modeles 3D des Traco Power
2020-06-01 Ajout resistance 620ohm 0603
2020-06-01 Maj PCB carte Alim (avec nouveau layer set)
2020-06-01 Ajout de la carte OPB620
2020-06-07 Premieres feuilles du schema de la carte mère.
2020-06-08 ajout de protection sur les lignes ADC et des bus pour les servo et capteurs
2020-06-14 Ajout de la feuille power et des connecteur sur les feuilles nucléo et DE0
2020-06-15 Ajout du pinout de la DE0 nano et ajout d'un connecteur pour la jauge batterie sur la carte alim
2020-06-19 Annotation de la CM et pré-positionnement connecteur Nano
2020-06-20 Modification des designators des cartes Herse et OPB. Correction position connecteur DE0, ajout de net color et netClass
2020-06-21 Premier placement sur la CM
2020-06-29 AJout d'une pull-up sur le NRST nucleo
2020-07-04 maj position connecteur carte mere
2020-07-05 Modification pinout Nucleo pour faciliter le routage, modification des connecteurs carte capteur
2020-07-05 Maj pinout
2020-07-11 avancement du routage live #22
2020-07-13 suite du routage de la carte-mère, modification des empreintes des ferrites.
2020-07-14 Suite routage carte mere, maj footprint ferrite carte alim et correction footprint colonnette wurth
2020-07-19 Routage carte mère live #23
2020-07-25 routage du live #24
2020-07-27 1iere passe d'optimisation
2020-07-28 suite optimisation
2020-07-28 routage du live #25
2020-07-29 ajout plan d'alim
2020-08-01 Maj HSI avant DNI
2020-08-04 ajout de la zone de masse pour 5P, sérigraphie (WIP)
2020-08-04 Ajout des DNI et Alternate, debut des corrections du DRC
2020-08-04 Assignation DNI et Alternate. debut correction DRC
2020-09-19 Correction des commits rates, ajout des fichiers sources après fab carte 2020
2020-09-19 ajout des fichiers de fab 2020
2020-10-11 maj des fix
2020-11-29 ajout de la carte conn batterie
2021-02-21 Correction d'un soucis d'alignement de symbole et maj routage Conn_blade
2021-12-02 Added TryOhm pcb project and 2022 workspace
2023-02-27 ajout archi elec 2023
    ajout brouillon archi elec 2023
    correction archi carte pneuma: ajout capteur T. i2c
2023-02-28 Update Architecture_Goldorak_2023.xml
    bloc places, reste à mettre les fils pour relier tout ça
2023-03-01 Update Architecture_Goldorak_2023.xml
    ajout des cables
2023-03-04 fixed crashing lib
    tentative de réparer la librairie de connecteur Molex qui a des problèmes avec les noms de composant suivant qui sont interprétés comme des dates par Altium :
    20-03-5035
    22-03-2021
    22-03-2031
    à voir si le changement des paramètres suffira ou si les composants devront être refait de zéro
2023-03-05 ajout de la carte Batterie
    basee sur le projet de la carte IPAV, cette carte assure l'interconnection des batteries Milwaukee M12 avec le reste du robot.
2023-03-26 ajout symbole-empreinte manquante
    - le SOIC custom
    - le connecteur Batterie (footprint à faire)
2023-03-26 debut placement carte Batterie
    et creation de l'empreinte Buzzer
2023-03-28 avancement placement
2023-03-28 fin du routage de la carte batterie
    reste à générer les fichiers de fab
2023-03-29 ajustement de la position des composants en fonction de la CAO de la piece 3D
2023-04-03 ajustement des pistes en fonction des risques meca
2023-04-11 fichier de prod carte batterie
2023-04-29 changement des couleurs de fil dans le schema avant correction
2023-04-29 correction alimentation LipoSaver
    un fil était manquant, ce fix ne couvre pas le comportement de la pin Cell2 des batteries Milwaukee
2023-05-02 fix CM AU_STATUT
    (oublié au commit précédent)
2023-07-23 Maj archi elec 2023
    ajout ventillo, capteur, carte LCD
2023-11-05 MaJ preference Altium
2024-02-03 creation projet carte alim turbines
2024-03-09 Carte Alim Turbines - Schema et Placement
2024-03-11 routage (part1) carte batterie PAMI
2024-03-12 Ajout des plans au routage de la carte batterie PAMI
2024-03-13 Work in progress
2024-03-13 Création de la carte mère PAMI 2024
2024-03-13 ajout d'une grossiere proposition de placement
2024-03-15 schema et routage (premiere version) de la carte miniPAMI
2024-03-16 fin routage carte mini-PAMI
2024-03-17 Carte Mère PAMI - Work In Progress
2024-03-17 fin routage Carte Turbine
    et ajout doc Kicad
2024-03-18 petite correction avant generation du dossier
2024-03-19 CM PAMI 2024 - WIP
2024-03-19 generation des fichiers de fabrication des cartes
2024-03-21 fin routage carte Mere PAMI
2024-03-21 correction de l'empreinte du mouvement tracker (690357281076 au lieu de 690367281076)
2024-03-22 note sur un Patch du connecteur avec la carte alim PAMI
2024-03-23 CM PAMI 2024 - Propretés sur le schéma
2024-03-30 Generation de la documentation - part 1
2024-03-30 generation de la documentation - part 2
2024-03-30 oublie de fichier lock et temporaire
2025-03-18 Mise à jour carte MiniPAMI
    application des modifications identifiée en 2024
    - suppression des options '1 ou 2 mosfet'
    - suppression de la selection de delais, remplace par un potentiometre
    - suppression de la prise du uSW IDLE (desormais cable en serie avec l'AU)
    - remplacement de la prise mot2 par une prise mot Fete
    - retablissement de la diode dans la BOM
2025-03-24 Ajout ref JLCPCB
2025-06-07 creation du schema carte mere PAMI 2025
2025-06-08 préplacement carte PAMI 2025
2025-06-09 fin du routage carte PAMI 2025
2025-06-09 modification de bouton et fichier de prod
